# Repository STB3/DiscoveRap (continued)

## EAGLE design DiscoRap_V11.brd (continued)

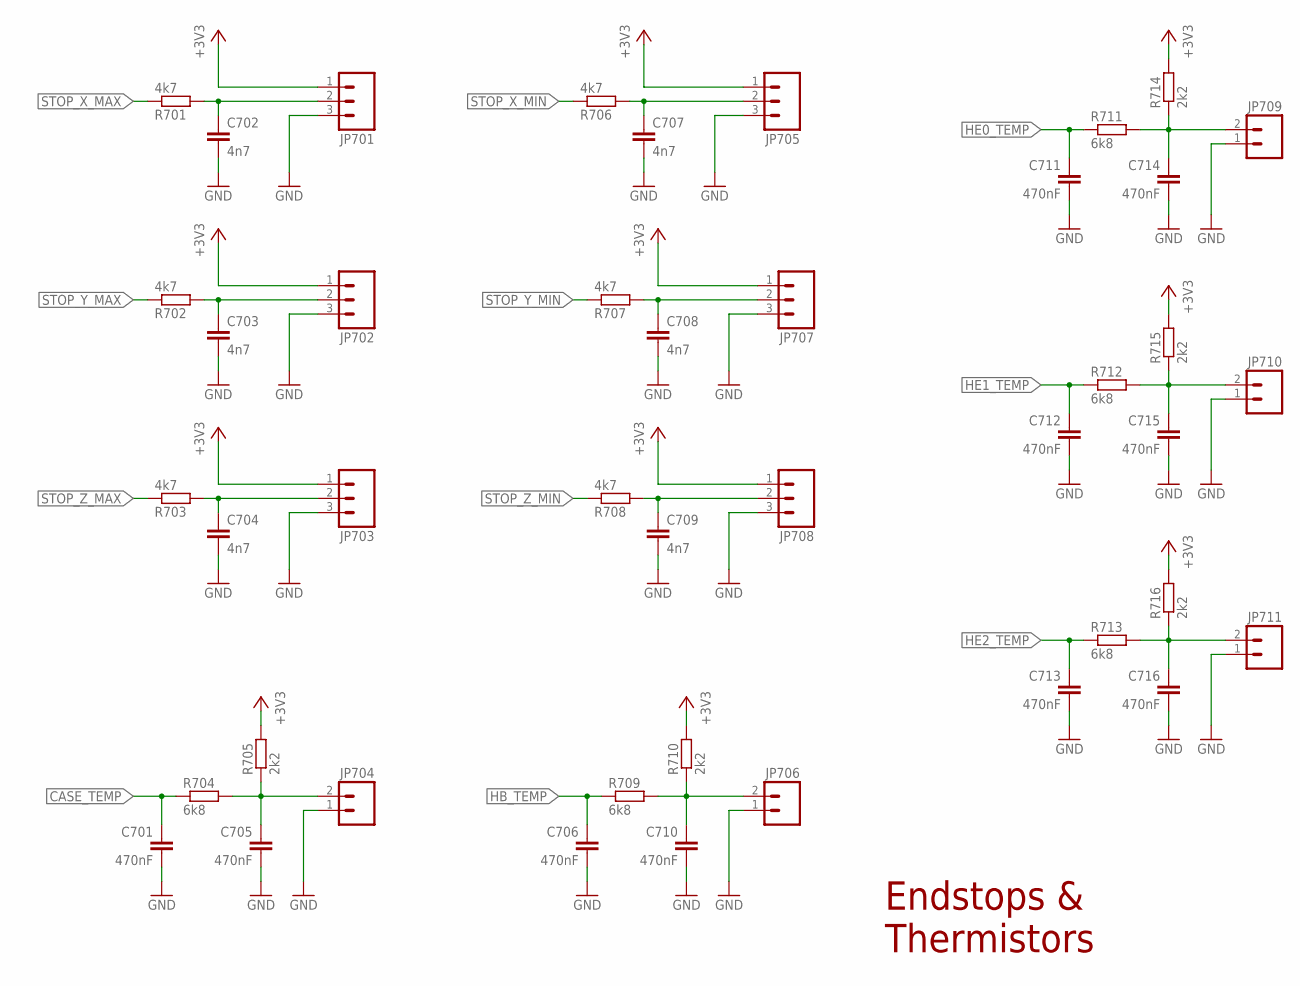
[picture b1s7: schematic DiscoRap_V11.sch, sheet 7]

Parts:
C701, C705, C706, C710, C711, C712, C713, C714, C715, C716: 470nF; 0805
C702, C703, C704, C707, C708, C709: 4n7; 0805
JP701, JP702, JP703, JP705, JP707, JP708: M03POLAR; MOLEX-1X3
JP704, JP706, JP709, JP710, JP711: M02POLAR; MOLEX-1X2
R701, R702, R703, R706, R707, R708: 4k7; 0805
R704, R709, R711, R712, R713: 6k8; 0805
R705, R710, R714, R715, R716: 2k2; 0805

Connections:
+3V3: JP701.1, JP702.1, JP703.1, JP705.1, JP707.1, JP708.1, R705.2, R710.2, R714.2, R715.2, R716.2; also elsewhere on the board
CASE_TEMP: C701.1, R704.1; also elsewhere on the board
GND: C701.2, C702.2, C703.2, C704.2, C705.2, C706.2, C707.2, C708.2, C709.2, C710.2, C711.2, C712.2, C713.2, C714.2, C715.2, C716.2, JP701.3, JP702.3, JP703.3, JP704.1, JP705.3, JP706.1, JP707.3, JP708.3, JP709.1, JP710.1, JP711.1; also elsewhere on the board
HB_TEMP: C706.1, R709.1; also elsewhere on the board
HE0_TEMP: C711.1, R711.1; also elsewhere on the board
HE1_TEMP: C712.1, R712.1; also elsewhere on the board
HE2_TEMP: C713.1, R713.1; also elsewhere on the board
unnamed: C702.1, JP701.2, R701.2
unnamed: C703.1, JP702.2, R702.2
unnamed: C704.1, JP703.2, R703.2
unnamed: C709.1, JP708.2, R708.2
unnamed: C708.1, JP707.2, R707.2
unnamed: C707.1, JP705.2, R706.2
unnamed: C710.1, JP706.2, R709.2, R710.1
unnamed: C714.1, JP709.2, R711.2, R714.1
unnamed: C715.1, JP710.2, R712.2, R715.1
unnamed: C716.1, JP711.2, R713.2, R716.1
unnamed: C705.1, JP704.2, R704.2, R705.1
STOP_X_MAX: R701.1; also elsewhere on the board
STOP_X_MIN: R706.1; also elsewhere on the board
STOP_Y_MAX: R702.1; also elsewhere on the board
STOP_Y_MIN: R707.1; also elsewhere on the board
STOP_Z_MAX: R703.1; also elsewhere on the board
STOP_Z_MIN: R708.1; also elsewhere on the board

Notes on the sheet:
Endstops & Thermistors

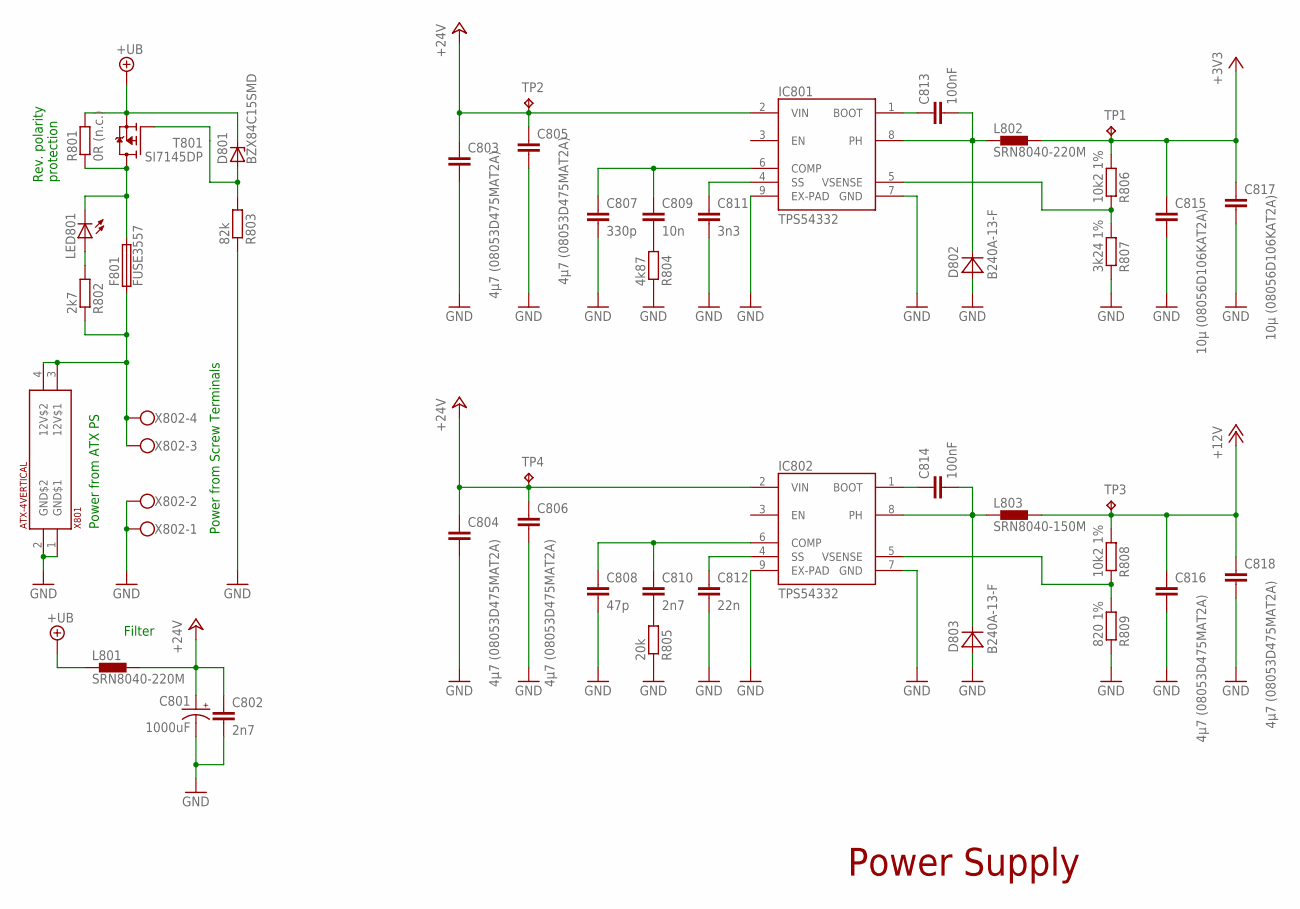
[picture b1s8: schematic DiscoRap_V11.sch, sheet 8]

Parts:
C801: 1000uF; CPOL-RADIAL-1000UF-25V
C802, C810: 2n7; 0805
C803, C804, C805, C806, C816, C818: 4µ7 (08053D475MAT2A); 0805
C807: 330p; 0805
C808: 47p; 0805
C809: 10n; 0805
C811: 3n3; 0805
C812: 22n; 0805
C813, C814: 100nF; 0805
C815, C817: 10µ (08056D106KAT2A); 0805
D801: BZX84C15SMD; TO236
D802, D803: B240A-13-F; SMA
F801: FUSE3557; 3557
IC801, IC802: TPS54332; PDSO-G8
L801, L802: SRN8040-220M; SRN8040
L803: SRN8040-150M; SRN8040
LED801: LEDCHIPLED_0805; CHIPLED_0805
R801: 0R (n.c.); R2512
R802: 2k7; 0805
R803: 82k; 0805
R804: 4k87; 0805
R805: 20k; 0805
R806, R808: 10k2 1%; 0805
R807: 3k24 1%; 0805
R809: 820 1%; 0805
T801: SI7145DP; SO-8_POWERPACK
TP1, TP2, TP3, TP4: TPB1,27; B1,27
X801: ATX-4VERTICAL; MINIFITJR-4-VERTICAL
X802: W237-4

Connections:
+3V3: C815.1, C817.1, L802.2, R806.2, TP1.TP; also elsewhere on the board
+12V: C816.1, C818.1, L803.2, R808.2, TP3.TP; also elsewhere on the board
+24V: C801.1 (+), C802.1, C803.1, C804.1, C805.1, C806.1, IC801.2 (VIN), IC802.2 (VIN), L801.2, TP2.TP, TP4.TP
+UB: D801.C, L801.1, R801.2, T801.1 (S), T801.2 (S), T801.3 (S); also elsewhere on the board
GND: C801.2 (-), C802.2, C803.2, C804.2, C805.2, C806.2, C807.2, C808.2, C811.2, C812.2, C815.2, C816.2, C817.2, C818.2, D802.A, D803.A, IC801.7 (GND), IC801.9 (EX-PAD), IC802.7 (GND), IC802.9 (EX-PAD), R803.1, R804.1, R805.1, R807.1, R809.1, X801.1 (GND$1), X801.2 (GND$2), X802.1, X802.2; also elsewhere on the board
unnamed: C809.2, R804.2
unnamed: C811.1, IC801.4 (SS)
unnamed: C813.1, IC801.1 (BOOT)
unnamed: C814.2, D803.C, IC802.8 (PH), L803.1
unnamed: IC802.5 (VSENSE), R808.1, R809.2
unnamed: C808.1, C810.1, IC802.6 (COMP)
unnamed: C810.2, R805.2
unnamed: C812.1, IC802.4 (SS)
unnamed: C814.1, IC802.1 (BOOT)
unnamed: C813.2, D802.C, IC801.8 (PH), L802.1
unnamed: IC801.5 (VSENSE), R806.1, R807.2
unnamed: C807.1, C809.1, IC801.6 (COMP)
unnamed: D801.A, R803.2, T801.4 (G)
unnamed: F801.1, F801.2 (1), R802.1, X801.3 (12V$1), X801.4 (12V$2), X802.3, X802.4
unnamed: F801.3 (2), F801.4 (2), LED801.C, R801.1, T801.5 (D), T801.6 (D), T801.7 (D), T801.8 (D), T801.EXP_PAD (D)
unnamed: LED801.A, R802.2

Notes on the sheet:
Power Supply
Power from ATX PS
Power from Screw Terminals
Rev. polarity protection
Filter

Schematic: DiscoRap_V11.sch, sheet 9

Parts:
H901, H902, H903, H904: MOUNT-HOLE3.2; 3,2
JP901: PINHD-2X3; 2X03
JP902: M02POLAR; MOLEX-1X2
R901, R902, R903: 3k3; 0805

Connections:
+3V3: JP901.2; also elsewhere on the board
AUX_IN_0: JP901.1; also elsewhere on the board
AUX_IN_1: JP901.3; also elsewhere on the board
AUX_IN_2: JP901.5; also elsewhere on the board
EMERGENCY_STOP: JP902.2; also elsewhere on the board
GND: JP901.4, JP901.6, JP902.1, R901.1, R902.1, R903.1; also elsewhere on the board
MISO: R901.2; also elsewhere on the board
MOSI: R902.2; also elsewhere on the board
SCK: R903.2; also elsewhere on the board

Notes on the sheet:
Other

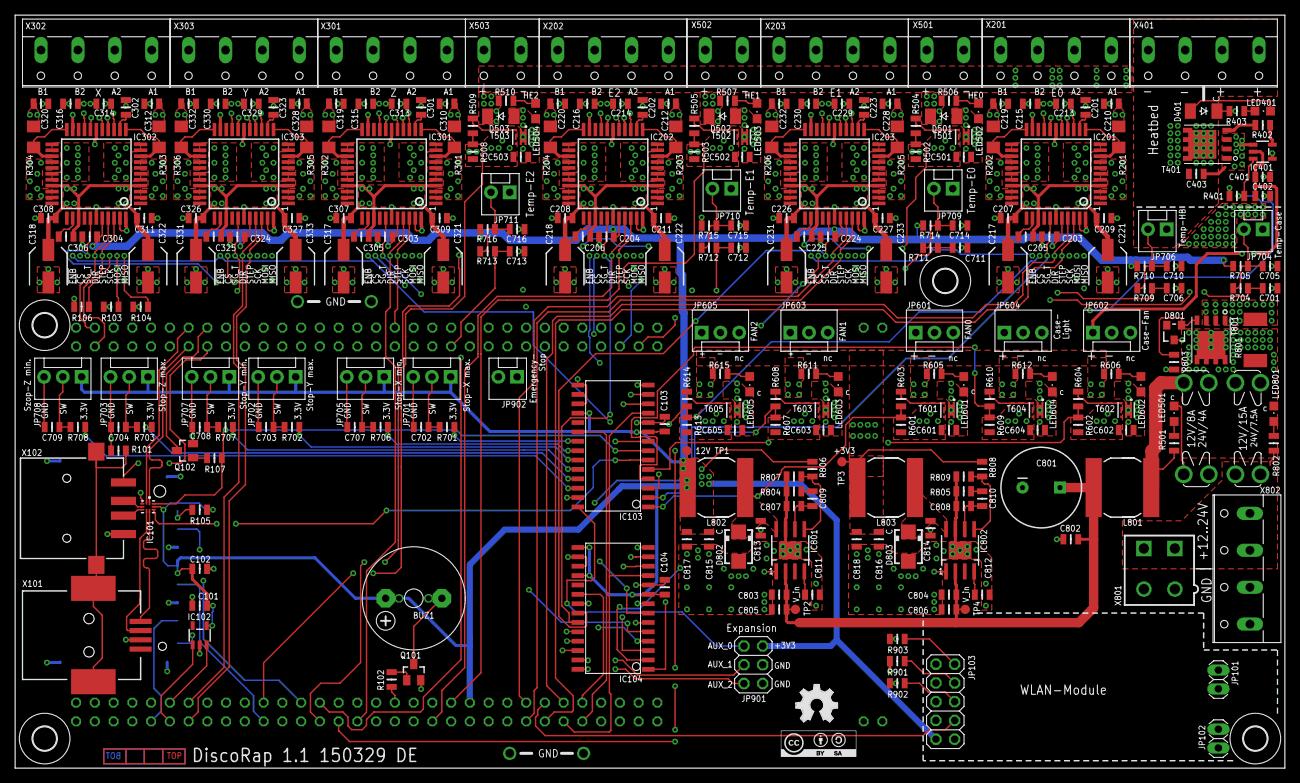
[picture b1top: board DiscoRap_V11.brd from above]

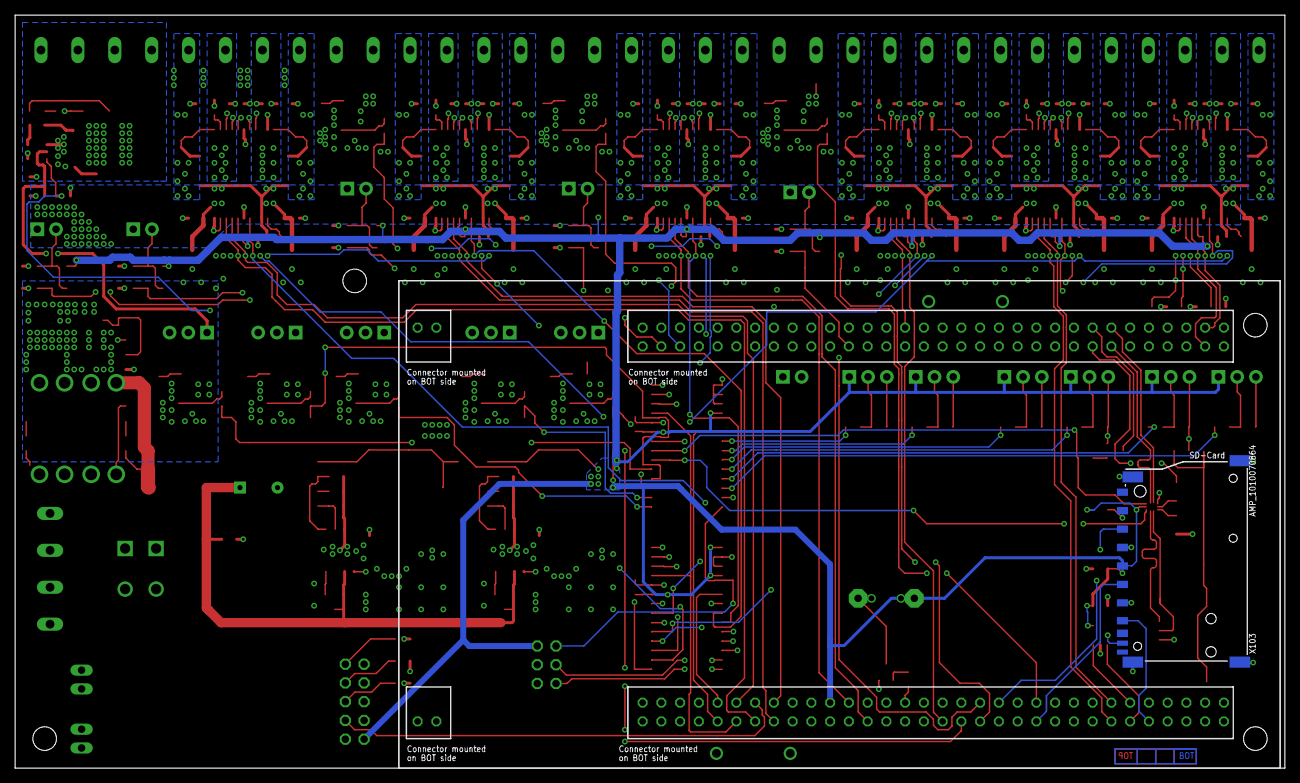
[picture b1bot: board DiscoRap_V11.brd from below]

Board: 4 copper layers, 172.0 x 102.0 mm, 286 parts (2 on the bottom side), 190 nets.

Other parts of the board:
LOGO1: OSHW_LOGO_FILLX0200-NT; OSHW_FILLX200_NOTEXT
U$3: CC-BY-SA

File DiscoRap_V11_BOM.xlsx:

Bill of Material for DiscoRap V1.1
Qty | Value | Tolerance | Voltage | Other | Device | Package | Parts | Description | Manufacturer | Manufacturer Part No. | Mouser | Digikey
11 | Green |  |  | standard 10..20mA | LED | 0805 | LED401, LED501, LED502, LED503, LED504, LED601, LED602, LED603, LED604, LED605,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 | LED
6 | Molex Serie 6373 |  |  |  | M02POLAR | MOLEX-1X2 | JP704, JP706, JP709, JP710, JP711, JP902 | Molex Serie 6373 | Molex | 22-23-2021 | 538-22-23-2021
11 | Molex Serie 6373 |  |  |  | M03POLAR | MOLEX-1X3 | JP601, JP602, JP603, JP604, JP605, JP701, JP702, JP703, JP705, JP707, JP708 | Molex Serie 6373 | Molex | 22-23-2031 | 538-22-23-2031
2 |  |  |  |  | Pinheader 1x2 | RM 2.54mm | JP101, JP102 | PIN HEADER
1 |  |  |  |  | Pinheader 2x3 | RM 2.54mm | JP901 | PIN HEADER
1 |  |  |  |  | Pinheader 2x5 | RM 2.54mm | JP103 | PIN HEADER
3 |  |  |  |  | Screw Clamp 2 pol. | RM5.00 | X501, X502, X503 | Screw Clamp | Phoenix Contact | 1935161 | 651-1935161
8 |  |  |  |  | Screw Clamp 4 pol. | W237-4 | X201, X202, X203, X301, X302, X303, X401, X802 | Screw Clamp | Phoenix Contact | 1935187 | 651-1935187
0 | n.c. |  |  | not populated | Resistor | 2512 | R801 | Resistor
12 | 0R15 | 1% |  | 500mW | Resistor | 1206 | R201, R202, R203, R204, R205, R206, R301, R302, R303, R304, R305, R306 | Resistor | Panasonic | ERJ-8BSFR15V | 667-ERJ-8BSFR15V
9 | 100 | 5% |  |  | Resistor | 0805 | R402, R504, R505, R509, R603, R604, R608, R610, R614
1 | 1000uF | 20% | min. 30V |  | Electrolytic Capacitor | RM 5mm / Diameter < 11.5mm | C801 | Electrolytic Capacitor
9 | 100k | 5% |  |  | Resistor | 0805 | R401, R502, R503, R508, R601, R602, R607, R609, R613 | Resistor
7 | 100nF | 10% | min. 25V | X7R | Capacitor | 0805 | C101, C102, C103, C104, C401, C813, C814 | Capacitor
18 | 100nF |  | min. 50V | X7R | Capacitor | 0805 | C203, C204, C207, C208, C209, C211, C224, C226, C227, C303, C304, C307, C308, C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 | Capacitor
24 | 100p |  | min. 63V | NP0 | Capacitor | 0805 | C210, C212, C213, C214, C215, C216, C219, C220, C228, C229, C230, C232, C310, C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 | Capacitor
7 | 10k |  |  |  | Resistor | 0805 | R101, R102, R103, R104, R105, R106, R107 | Resistor
2 | 10k2 | 1% |  |  | Resistor | 0805 | R806, R808 | Resistor
1 | 10nF |  | min. 30V | X7R | Capacitor | 0805 | C809 | Capacitor
2 | 10µ | 10% | 6.3V | X5R | Capacitor | 0805 | C815, C817 | Capacitor | AVX | 08056D106KAT2A | 581-08056D106K
1 | 20k | 1% |  |  | Resistor | 0805 | R805 | Resistor
6 | 220nF | 10% | min. 16V |  | Capacitor | 0805 | C205, C206, C225, C305, C306, C325 | Capacitor
1 | 22n | 10% | min. 16V |  | Capacitor | 0805 | C812 | Capacitor
12 | 22µF | 20% | min. 35V | Ripple current >150mA | Electrolytic Capacitor | SMD B6 (6.3 x 5.3 mm²) | C217, C218, C221, C222, C231, C233, C317, C318, C321, C322, C331, C333 | Electrolytic Capacitor | KEMET | EEV226M035A9DAA | 80-EEV226M035A9DAA
1 | 8kBit serial eePROM |  |  |  | eePROM | SOT23-5L | IC102 | Serial EEPROM | Microchip | 24LC08BT-I/OT | 579-24LC08BT-I/OT
5 | 2k2 | 1% |  |  | Resistor | 0805 | R705, R710, R714, R715, R716 | Resistor
11 | 2k7 | 5% |  |  | Resistor | 0805 | R403, R501, R506, R507, R510, R605, R606, R611, R612, R615, R802 | Resistor
2 | 2n7 | 10% |  |  | Capacitor | 0805 | C802, C810 | Capacitor
1 | 2u2 | 20% | min. 16V |  | Capacitor | 0805 | C402 | Capacitor
1 | 330p | 10% |  |  | Capacitor | 0805 | C807 | Capacitor
1 | 3k24 | 1% |  |  | Resistor | 0805 | R807 | Resistor
3 | 3k3 | 5% |  |  | Resistor | 0805 | R901, R902, R903 | Resistor
1 | 3n3 | 10% |  |  | Capacitor | 0805 | C811 | Capacitor
16 | 470nF | 10% | min. 10V |  | Capacitor | 0805 | C201, C202, C223, C301, C302, C323, C701, C705, C706, C710, C711, C712, C713, C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 | Capacitor
1 | 47p | 10% |  |  | Capacitor | 0805 | C808 | Capacitor
6 | 4k7 | 5% |  |  | Resistor | 0805 | R701, R702, R703, R706, R707, R708 | Resistor
1 | 4k87 | 1% |  |  | Resistor | 0805 | R804 | Resistor
15 | 4n7 | 10% | min. 35V |  | Capacitor | 0805 | C403, C501, C502, C503, C601, C602, C603, C604, C605, C702, C703, C704, C707, C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 | Capacitor
6 | 4µ7 | 20% | min. 25V | X5R | Capacitor | 0805 | C803, C804, C805, C806, C816, C818 | Capacitor | AVX | 08053D475MAT2A | 581-08053D475MAT2A
5 | 6k8 | 5% |  |  | Resistor | 0805 | R704, R709, R711, R712, R713 | Resistor
1 | 820 | 1% |  |  | Resistor | 0805 | R809 | Resistor
1 | 82k |  |  |  | Resistor | 0805 | R803 | Resistor
1 | AMP_1010070864 |  |  |  | AMP_1010070864 | AMP_1010070864 | X103 | Amphenol SD-Card Connector |  | 1010070864 | 523-101-00708-64
0 | n.c. |  |  | not populated | ATX-4VERTICAL | MINIFITJR-4-VERTICAL | X801
2 | B240A-13-F |  |  |  | Schottky Diode | SMA | D802, D803 | Surface Mount Schottky Power Rectifier | Diodes Inc. | B240A-13-F | 621-B240A-F
2 | BC817-25 |  |  |  | Transistor NPN | SOT23-BEC | Q101, Q102 | NPN Transistor
1 | BZX84C15 |  |  |  | Zener Diode 15V | TO236 | D801 | Zener Diode 15V | Fairchild | BZX84C15
4 | S1G-E3/5AT |  |  |  | Rectifier Diode | SMA | D401, D501, D502, D503 | Rectifier Diode | Vishay | S1G-E3/5AT | 625-S1G-E3/5AT
1 | DG2722 |  |  |  | USB Switch | MINI_QFN_10L | IC101 | USB Switch | Vishay | DG2722DN-T1-E4 | 781-DG2722DN-E4
1 | Buzzer |  | 3.3V |  | Buzzer | RM4 / RM7.6 | BUZ1 | Buzzer | Mallory | PB-09N23P-03Q | 539-PB09N23P-03Q
4 | FUSE3557 |  |  |  | Fuseholder | 3557 | F501, F801 | Fuseholder | Keystone Electronics | 3557 | 534-3557
1 | MCP1402 |  |  |  | MCP1402 | SOT23-5L | IC401 | MOSFET driver | Microchip | MCP1402T-E/OT | 579-MCP1402T-E/OT
2 | MCP23S17SO |  |  |  | MCP23S17SO | SO28W | IC103, IC104 | SPI Port Expander | Microchip | MCP23S17T-E/SO | 579-MCP23S17T-E/SO
1 | SI7145DP |  |  |  | SI7145DP | SO-8_POWERPACK | T801 | P-Ch. MOSFET 2.6mOhm -30V | Vishay | SI7145DP-T1-GE3 | 781-SI7145DP-GE3
8 | SIA400EDJ |  |  |  | SIA400EDJ | SC70-6L | T501, T502, T503, T601, T602, T603, T604, T605 | N-Ch. MOSFET 19mOhm 30V | Vishay | SIA400EDJ-T1-GE3 | 78-SIA400EDJ-T1-GE3
1 | SIR416DP |  |  |  | SIR416DP | SO-8_POWERPACK | T401 | N-Ch. MOSFET 3.8mOhm 40V | Vishay | SIR416DP-GE3 | 781-SIR416DP-GE3
1 | SRN8040-150M |  |  |  | SRN8040 | SRN8040 | L803 | Bourns Power Inductors 15uH/2.4A |  | SRN8040-150M | 652-SRN8040-150M
2 | SRN8040-220M |  |  |  | SRN8040 | SRN8040 | L801, L802 | Bourns Power Inductors 22uH/2.4A |  | SRN8040-220M | 652-SRN8040-220M
2 | Pfostenbuchse | solder side ! |  |  | 32x2 | RM 2.54mm
2 | Pfostenbuchse | solder side ! |  |  | 1x2 | RM 2.54mm
1 | TE_292303-9 |  |  |  | TE_292303-9 | TE_USB_A_SMD | X102 | TE Connectivity USB-A | TE Connectivity | 292303-9 | 571-292303-9
6 | TMC260 |  |  |  | TMC260 | SQFP-S-10X10-44 | IC201, IC202, IC203, IC301, IC302, IC303 | Stepper Driver | Trinamic | TMC260-PA-T |  | 1460-1070-1-ND
2 | TPS54332 |  |  |  | TPS54332 | PDSO-G8 | IC801, IC802 | TPS54332 | Texas Instruments | TPS54332DDAR | 595-TPS54332DDAR
1 | USB-B_SMD |  |  |  | USB-B_SMD | USB_B_SMD | X101 |  |  | KUSBEX-SMT-BS1N-BTR | 806-KUSBEXSMTBS1NBTR
 | Changes | Date | Vers. | Author
 | Initial Version | 29.03.2015 | 1.1 | DE

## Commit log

2015-04-05 :neckbeard: Added .gitattributes
2015-04-05 DiscoveRap initial PCB Version
2015-04-05 DiscoveRap initial PCB release
2015-04-05 BOM for DiscoveRap
2015-04-15 Add schematics in pdf format
